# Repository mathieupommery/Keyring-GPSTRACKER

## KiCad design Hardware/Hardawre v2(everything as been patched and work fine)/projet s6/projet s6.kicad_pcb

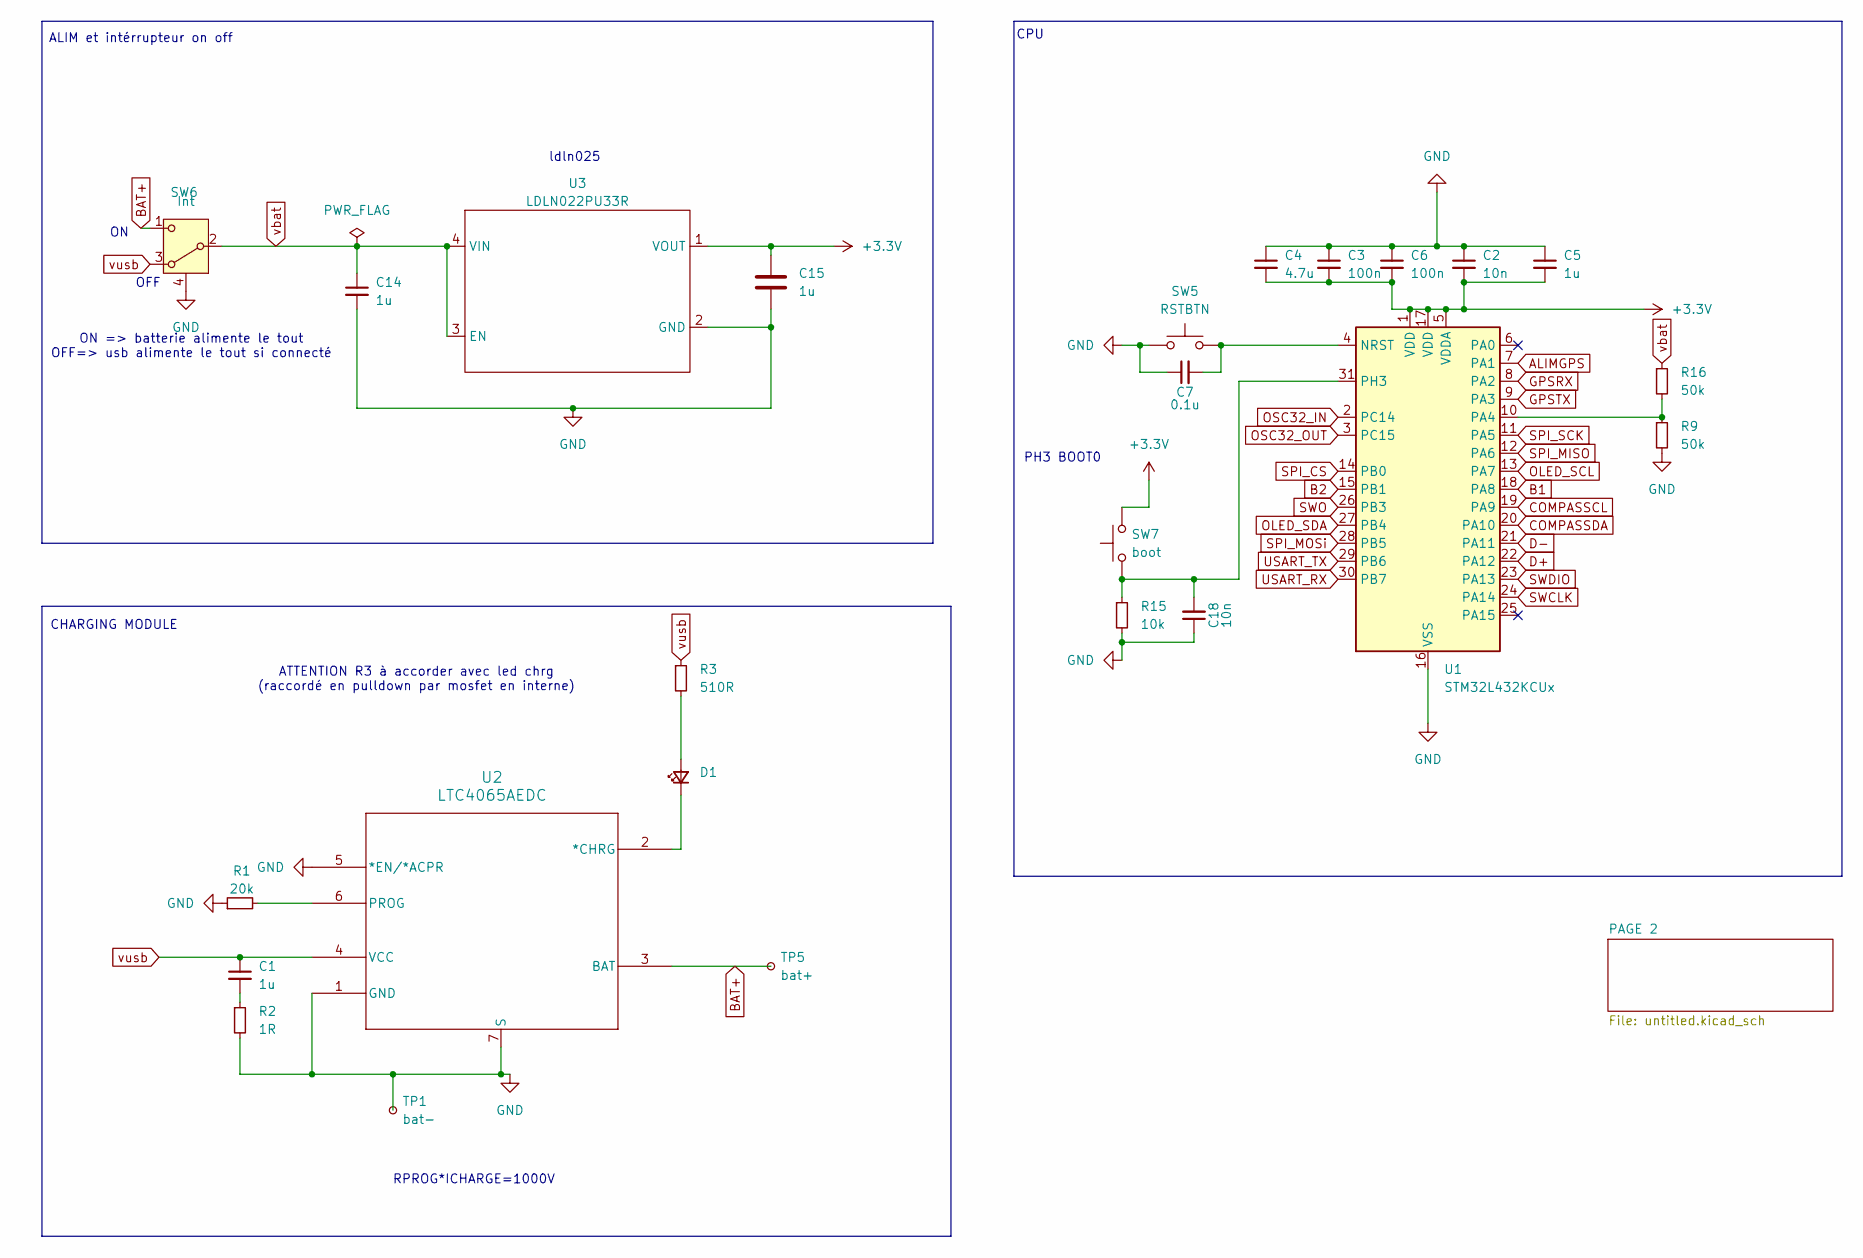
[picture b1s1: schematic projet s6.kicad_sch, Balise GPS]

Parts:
C1, C5, C14, C15: 1u; C_0402_1005Metric_Pad0.74x0.62mm_HandSolder
C2, C18: 10n; C_0402_1005Metric_Pad0.74x0.62mm_HandSolder
C3, C6: 100n; C_0402_1005Metric_Pad0.74x0.62mm_HandSolder
C4: 4.7u; C_0402_1005Metric_Pad0.74x0.62mm_HandSolder
C7: 0.1u; C_0402_1005Metric_Pad0.74x0.62mm_HandSolder
D1: LED_0201_0603Metric_Pad0.64x0.40mm_HandSolder
R1: 20k; R_0402_1005Metric_Pad0.72x0.64mm_HandSolder
R2: 1R; R_0402_1005Metric_Pad0.72x0.64mm_HandSolder
R3: 510R; R_0402_1005Metric_Pad0.72x0.64mm_HandSolder
R9, R16: 50k; R_0402_1005Metric_Pad0.72x0.64mm_HandSolder
R15: 10k; R_0402_1005Metric_Pad0.72x0.64mm_HandSolder
SW5: RSTBTN; SW_KXT3
SW6: Int; SW_PCM
SW7: boot; SW_KXT3
TP1: bat-; TestPoint_THTPad_D1.0mm_Drill0.5mm
TP5: bat+; TestPoint_THTPad_D1.0mm_Drill0.5mm
U1: STM32L432KCUx; QFN-32-1EP_5x5mm_P0.5mm_EP3.45x3.45mm
U2: LTC4065AEDC; DFN-6_DC_LIT
U3: LDLN022PU33R; LDLN025PU33R

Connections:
+3.3V: C2.2, C3.2, C4.2, C5.2, C6.2, C15.1, SW7.2, U1.1 (VDD), U1.5 (VDDA), U1.17 (VDD), U3.1 (VOUT); also elsewhere on the board
ALIMGPS: U1.7 (PA1); also elsewhere on the board
B1: U1.18 (PA8); also elsewhere on the board
B2: U1.15 (PB1); also elsewhere on the board
BAT+: SW6.1 (C), TP5.1, U2.3 (BAT)
COMPASSCL: U1.19 (PA9); also elsewhere on the board
COMPASSDA: U1.20 (PA10); also elsewhere on the board
D+: U1.22 (PA12); also elsewhere on the board
D-: U1.21 (PA11); also elsewhere on the board
GND: C2.1, C3.1, C4.1, C5.1, C6.1, C7.1, C14.2, C15.2, C18.1, R1.1, R2.2, R9.2, R15.2, SW5.1, SW6.4 (S), TP1.1, U1.16 (VSS), U1.32 (VSS), U1.33 (VSS), U2.1 (GND), U2.5 (*EN/*ACPR), U2.7 (S), U3.2 (GND); also elsewhere on the board
GPSRX: U1.8 (PA2); also elsewhere on the board
GPSTX: U1.9 (PA3); also elsewhere on the board
unnamed: C1.2, R2.1
unnamed: D1.2 (A), R3.2
unnamed: D1.1 (K), U2.2 (*CHRG)
unnamed: C7.2, SW5.2, U1.4 (NRST)
unnamed: R9.1, R16.2, U1.10 (PA4)
unnamed: C18.2, R15.1, SW7.1, U1.31 (PH3)
unnamed: R1.2, U2.6 (PROG)
OLED_SCL: U1.13 (PA7); also elsewhere on the board
OLED_SDA: U1.27 (PB4); also elsewhere on the board
OSC32_IN: U1.2 (PC14)
OSC32_OUT: U1.3 (PC15)
SPI_CS: U1.14 (PB0); also elsewhere on the board
SPI_MISO: U1.12 (PA6); also elsewhere on the board
SPI_MOSi: U1.28 (PB5); also elsewhere on the board
SPI_SCK: U1.11 (PA5); also elsewhere on the board
SWCLK: U1.24 (PA14)
SWDIO: U1.23 (PA13)
SWO: U1.26 (PB3)
USART_RX: U1.30 (PB7); also elsewhere on the board
USART_TX: U1.29 (PB6); also elsewhere on the board
vbat: C14.1, R16.1, SW6.2 (B), U3.3 (EN), U3.4 (VIN)
vusb: C1.1, R3.1, SW6.3 (A), U2.4 (VCC); also elsewhere on the board

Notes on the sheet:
PH3 BOOT0
CHARGING MODULE
OFF
ON => batterie alimente le tout OFF=> usb alimente le tout si connecté
ATTENTION R3 à accorder avec led chrg (raccordé en pulldown par mosfet en interne)
ldln025
ALIM et intérrupteur on off
RPROG*ICHARGE=1000V
CPU

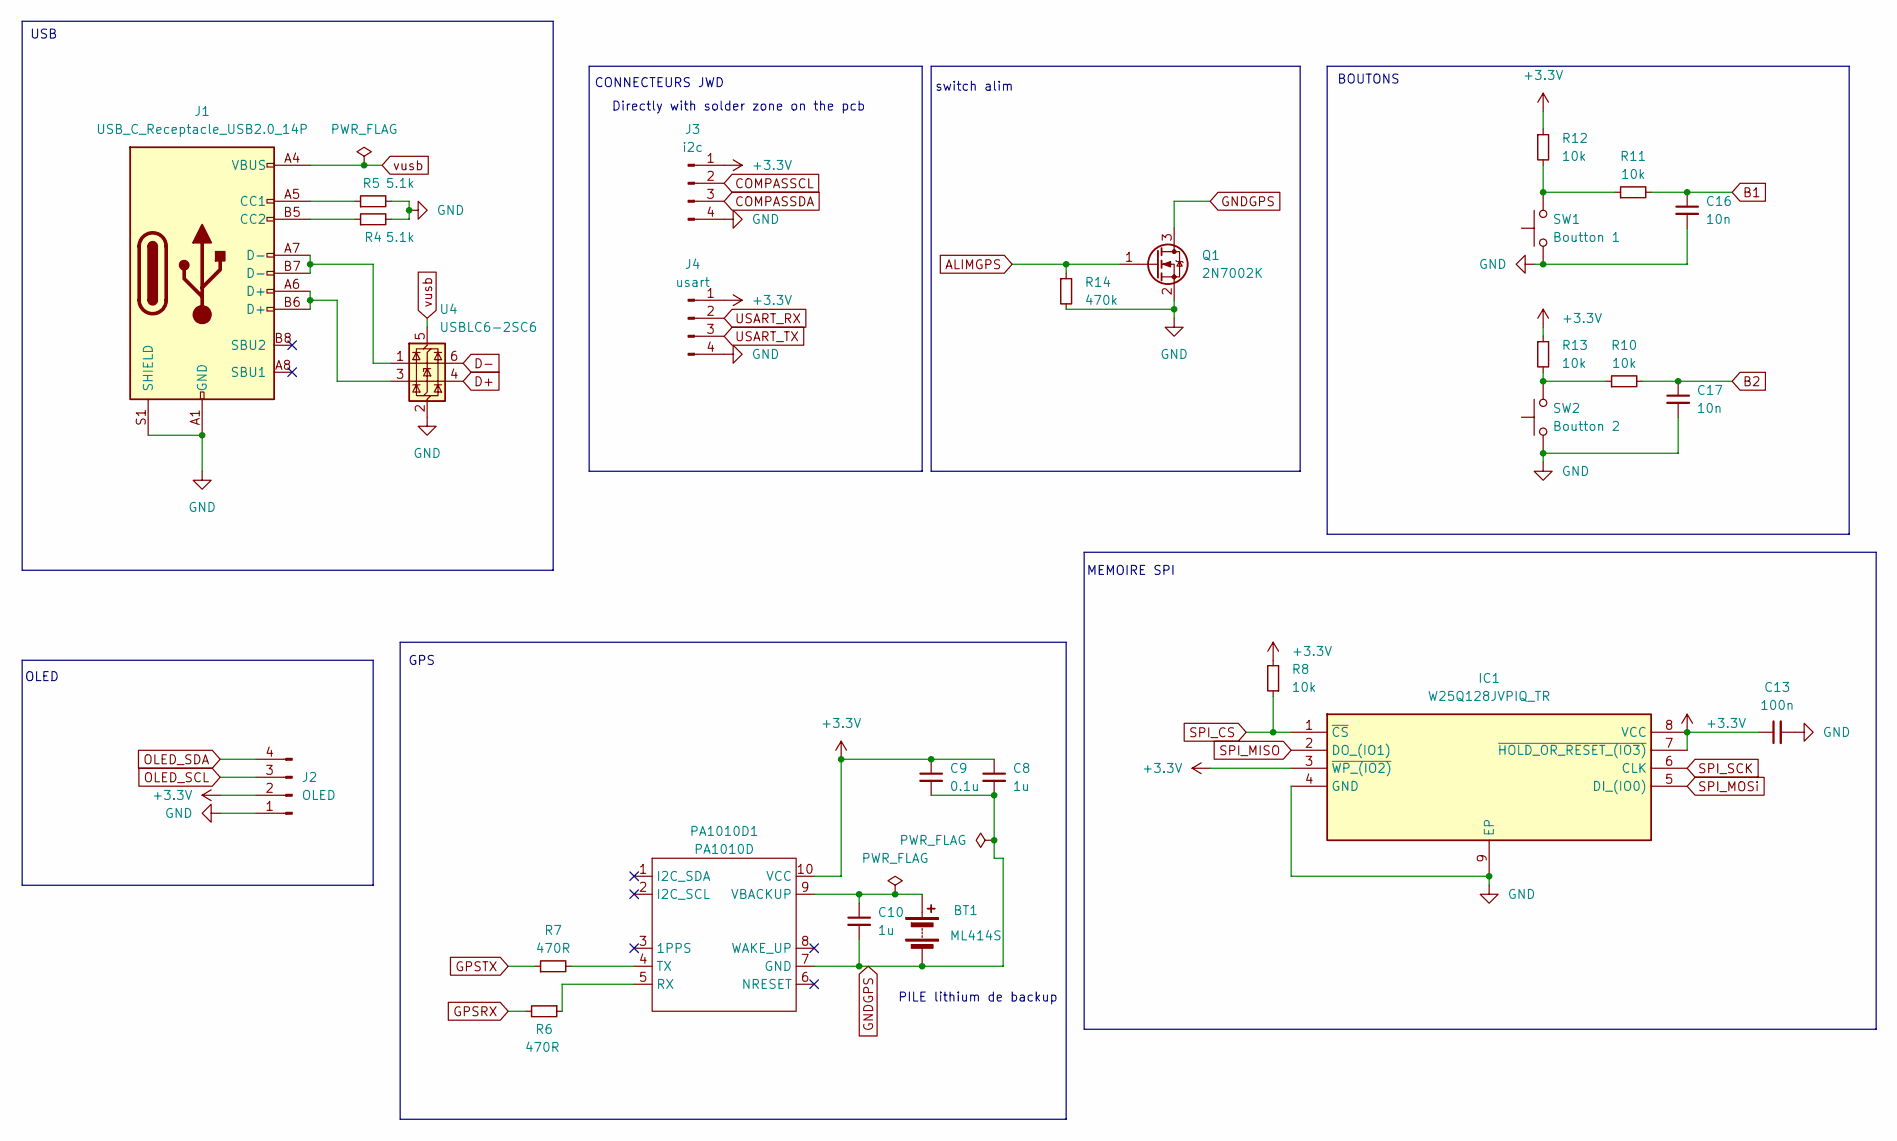
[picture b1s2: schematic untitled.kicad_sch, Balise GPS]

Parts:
BT1: ML414S; MS421R-IV03E
C8, C10: 1u; C_0402_1005Metric_Pad0.74x0.62mm_HandSolder
C9: 0.1u; C_0402_1005Metric_Pad0.74x0.62mm_HandSolder
C13: 100n; C_0402_1005Metric_Pad0.74x0.62mm_HandSolder
C16, C17: 10n; C_0402_1005Metric_Pad0.74x0.62mm_HandSolder
IC1: W25Q128JVPIQ_TR; SON127P600X500X80-9N-D; Manufacturer_Part_Number W25Q128JVPIQ TR; Mouser Part Number 454-W25Q128JVPIQTR
J1: USB_C_Receptacle_USB2.0_14P; USBC-WURTH
J2: OLED; PinSocket_1x04_P2.54mm_Vertical
J3: i2c; JST_SH_BM04B-SRSS-TB_1x04-1MP_P1.00mm_Vertical
J4: usart; JST_SH_BM04B-SRSS-TB_1x04-1MP_P1.00mm_Vertical
PA1010D1: PA1010D
Q1: 2N7002K; 2N7002KQB
R4, R5: 5.1k; R_0402_1005Metric_Pad0.72x0.64mm_HandSolder
R6, R7: 470R; R_0402_1005Metric_Pad0.72x0.64mm_HandSolder
R8, R10, R11, R12, R13: 10k; R_0402_1005Metric_Pad0.72x0.64mm_HandSolder
R14: 470k; R_0402_1005Metric_Pad0.72x0.64mm_HandSolder
SW1: Boutton 1; SW_PTS840
SW2: Boutton 2; SW_PTS840
U4: USBLC6-2SC6; SOT-23-6

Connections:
+3.3V: C8.1, C9.1, C13.1, IC1.3 (~WP_(IO2)), IC1.7 (~HOLD_OR_RESET_(IO3)), IC1.8 (VCC), J2.2, J3.1, J4.1, PA1010D1.10 (VCC), R8.2, R12.1, R13.1; also elsewhere on the board
ALIMGPS: Q1.1 (G), R14.1; also elsewhere on the board
B1: C16.1, R11.2; also elsewhere on the board
B2: C17.1, R10.2; also elsewhere on the board
COMPASSCL: J3.2; also elsewhere on the board
COMPASSDA: J3.3; also elsewhere on the board
D+: U4.4 (I/O2); also elsewhere on the board
D-: U4.6 (I/O1); also elsewhere on the board
GND: C13.2, C16.2, C17.2, IC1.4 (GND), IC1.9 (EP), J1.A1 (GND), J1.A12, J1.B1, J1.B12, J1.S1 (SHIELD), J2.1, J3.4, J3.MP, J4.4, J4.MP, Q1.2 (S), R4.2, R5.2, R14.2, SW1.1, SW2.1, U4.2 (GND); also elsewhere on the board
GNDGPS: BT1.2 (-), C8.2, C9.2, C10.2, PA1010D1.7 (GND), Q1.3 (D)
GPSRX: R6.2; also elsewhere on the board
GPSTX: R7.1; also elsewhere on the board
unnamed: BT1.1 (+), C10.1, PA1010D1.9 (VBACKUP)
unnamed: J1.A5 (CC1), R5.1
unnamed: J1.B5 (CC2), R4.1
unnamed: J1.A6 (D+), J1.B6 (D+), U4.3 (I/O2)
unnamed: J1.A7 (D-), J1.B7 (D-), U4.1 (I/O1)
unnamed: PA1010D1.5 (RX), R6.1
unnamed: PA1010D1.4 (TX), R7.2
unnamed: R10.1, R13.2, SW2.2
unnamed: R11.1, R12.2, SW1.2
OLED_SCL: J2.3; also elsewhere on the board
OLED_SDA: J2.4; also elsewhere on the board
SPI_CS: IC1.1 (~CS), R8.1; also elsewhere on the board
SPI_MISO: IC1.2 (DO_(IO1)); also elsewhere on the board
SPI_MOSi: IC1.5 (DI_(IO0)); also elsewhere on the board
SPI_SCK: IC1.6 (CLK); also elsewhere on the board
USART_RX: J4.2; also elsewhere on the board
USART_TX: J4.3; also elsewhere on the board
vusb: J1.A4 (VBUS), J1.A9, J1.B4, J1.B9, U4.5 (VBUS); also elsewhere on the board

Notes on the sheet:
PILE lithium de backup
OLED
MEMOIRE SPI
switch alim
GPS
Directly with solder zone on the pcb
USB
BOUTONS
CONNECTEURS JWD

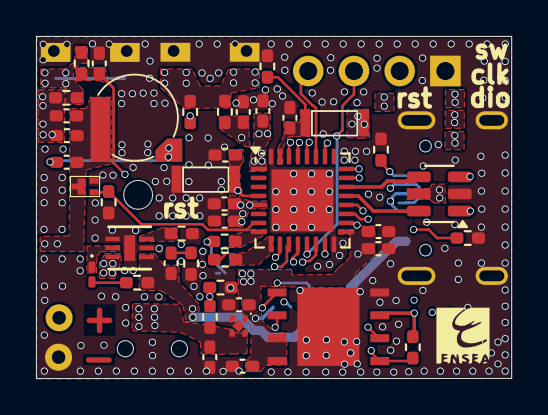
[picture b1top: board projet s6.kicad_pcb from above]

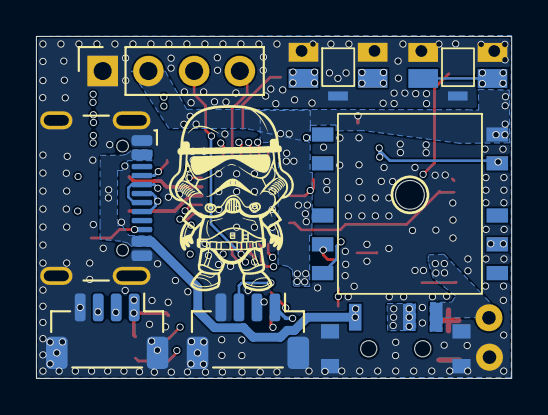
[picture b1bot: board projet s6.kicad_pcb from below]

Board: 4 copper layers, 26.4 x 19.0 mm, 52 parts (8 on the bottom side), 39 nets.

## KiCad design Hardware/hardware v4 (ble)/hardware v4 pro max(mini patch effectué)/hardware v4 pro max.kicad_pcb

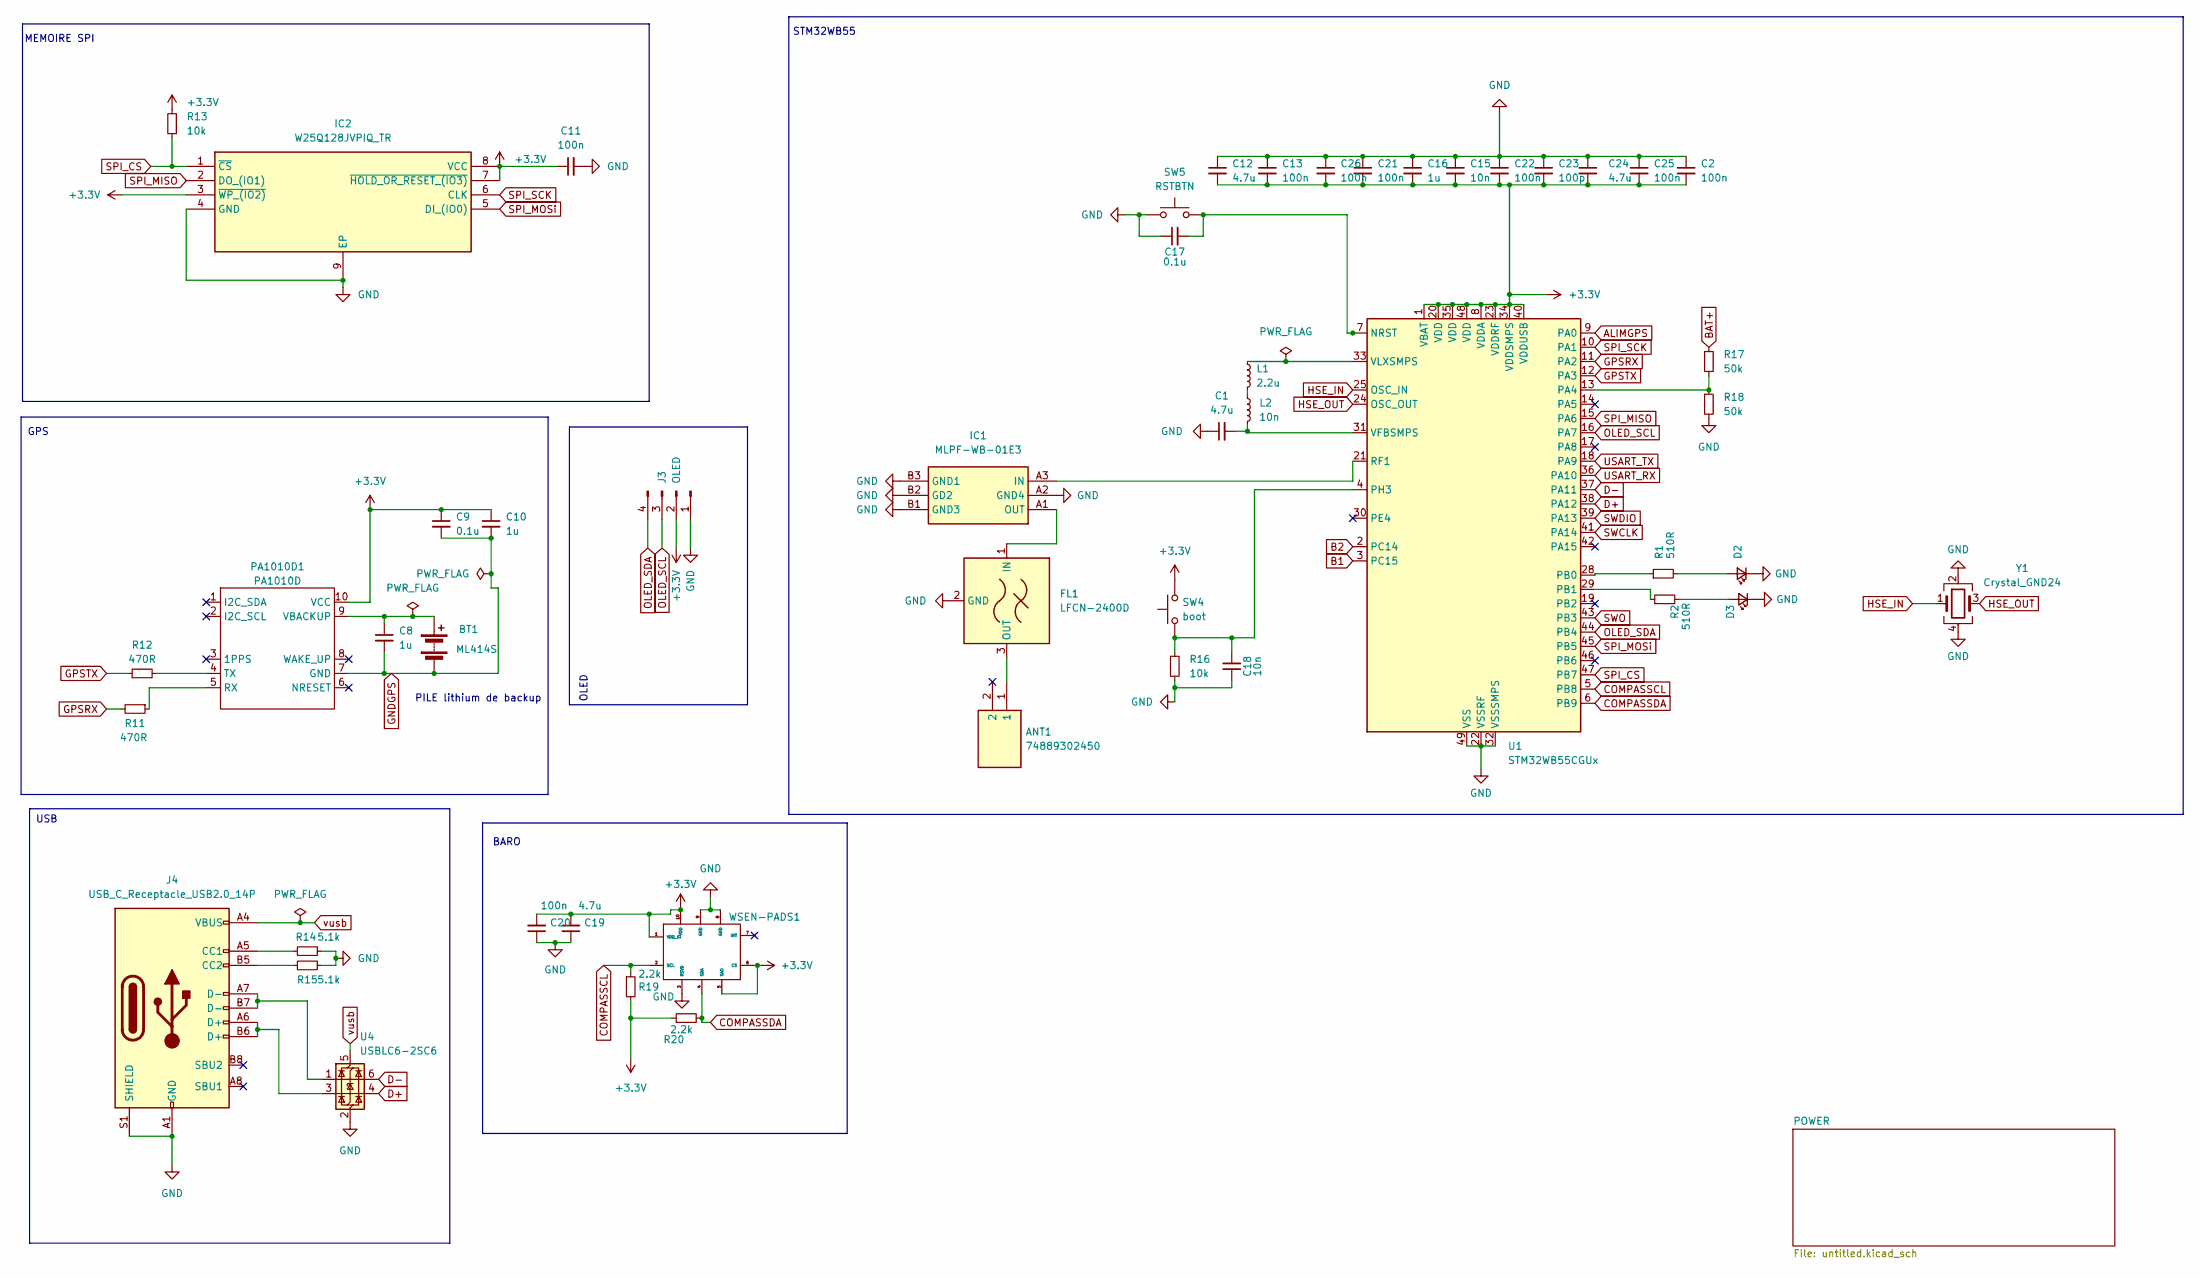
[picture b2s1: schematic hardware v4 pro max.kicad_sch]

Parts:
ANT1: 74889302450; Manufacturer_Part_Number 74889302450; Mouser Part Number 710-74889302450
BT1: ML414S; MS421R-IV03E
C1, C12, C19, C24: 4.7u; C_0402_1005Metric
C2, C11, C13, C20, C21, C22, C25, C26: 100n; C_0402_1005Metric
C8, C10, C16: 1u; C_0402_1005Metric
C9, C17: 0.1u; C_0402_1005Metric
C15, C18: 10n; C_0402_1005Metric
C23: 100p; C_0402_1005Metric
D2, D3: LED_0201_0603Metric_Pad0.64x0.40mm_HandSolder
FL1: LFCN-2400D; DLF162500LT5028A1
IC1: MLPF-WB-01E3; MLPFWB01E3; Manufacturer_Part_Number MLPF-WB-01E3; Mouser Part Number 511-MLPF-WB-01E3
IC2: W25Q128JVPIQ_TR; SON127P600X500X80-9N-D; Manufacturer_Part_Number W25Q128JVPIQ TR; Mouser Part Number 454-W25Q128JVPIQTR
J3: OLED; PinSocket_1x04_P2.54mm_Vertical
J4: USB_C_Receptacle_USB2.0_14P; USBC-WURTH
L1: 2.2u; L_0805_2012Metric
L2: 10n; L_0402_1005Metric
PA1010D1: PA1010D
R1, R2: 510R; R_0402_1005Metric
R11, R12: 470R; R_0402_1005Metric
R13, R16: 10k; R_0402_1005Metric
R14, R15: 5.1k; R_0402_1005Metric
R17, R18: 50k; R_0402_1005Metric
R19, R20: 2.2k; R_0402_1005Metric
SW4: boot; SW_KXT3
SW5: RSTBTN; SW_KXT3
U1: STM32WB55CGUx; QFN-48-1EP_7x7mm_P0.5mm_EP5.6x5.6mm
U4: USBLC6-2SC6; SOT-23-6
WSEN-PADS1: 2511020213301
Y1: Crystal_GND24; 830069494

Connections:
+3.3V: C2.2, C9.1, C10.1, C11.1, C12.2, C13.2, C15.2, C16.2, C19.2, C20.2, C21.2, C22.2, C23.2, C24.2, C25.2, C26.2, IC2.3 (~WP_(IO2)), IC2.7 (~HOLD_OR_RESET_(IO3)), IC2.8 (VCC), J3.2, PA1010D1.10 (VCC), R13.2, R19.2, R20.1, SW4.2, U1.1 (VBAT), U1.8 (VDDA), U1.20 (VDD), U1.23 (VDDRF), U1.34 (VDDSMPS), U1.35 (VDD), U1.40 (VDDUSB), U1.48 (VDD), WSEN-PADS1.1 (VDD_IO), WSEN-PADS1.5 (SAO), WSEN-PADS1.6 (CS), WSEN-PADS1.10 (VDD); also elsewhere on the board
ALIMGPS: U1.9 (PA0); also elsewhere on the board
B1: U1.3 (PC15); also elsewhere on the board
B2: U1.2 (PC14); also elsewhere on the board
BAT+: R17.1; also elsewhere on the board
COMPASSCL: R19.1, U1.5 (PB8), WSEN-PADS1.2 (SCL); also elsewhere on the board
COMPASSDA: R20.2, U1.6 (PB9), WSEN-PADS1.4 (SDA); also elsewhere on the board
D+: U1.38 (PA12), U4.4 (I/O2)
D-: U1.37 (PA11), U4.6 (I/O1)
GND: C1.1, C2.1, C11.2, C12.1, C13.1, C15.1, C16.1, C17.1, C18.1, C19.1, C20.1, C21.1, C22.1, C23.1, C24.1, C25.1, C26.1, D2.1 (K), D3.1 (K), FL1.2 (GND), FL1.4 (GND), IC1.A2 (GND4), IC1.B1 (GND3), IC1.B2 (GD2), IC1.B3 (GND1), IC2.4 (GND), IC2.9 (EP), J3.1, J4.A1 (GND), J4.A12, J4.B1, J4.B12, J4.S1 (SHIELD), R14.2, R15.2, R16.2, R18.2, SW5.1, U1.22 (VSSRF), U1.32 (VSSSMPS), U1.49 (VSS), U4.2 (GND), WSEN-PADS1.3 (RSVD), WSEN-PADS1.8 (GND), WSEN-PADS1.9 (GND), Y1.2, Y1.4; also elsewhere on the board
GNDGPS: BT1.2 (-), C8.2, C9.2, C10.2, PA1010D1.7 (GND); also elsewhere on the board
GPSRX: R11.2, U1.11 (PA2)
GPSTX: R12.1, U1.12 (PA3)
HSE_IN: U1.25 (OSC_IN), Y1.1
HSE_OUT: U1.24 (OSC_OUT), Y1.3
unnamed: BT1.1 (+), C8.1, PA1010D1.9 (VBACKUP)
unnamed: D2.2 (A), R1.2
unnamed: D3.2 (A), R2.2
unnamed: FL1.1 (IN), IC1.A1 (OUT)
unnamed: ANT1.1, FL1.3 (OUT)
unnamed: IC1.A3 (IN), U1.21 (RF1)
unnamed: J4.A5 (CC1), R14.1
unnamed: J4.B5 (CC2), R15.1
unnamed: J4.A6 (D+), J4.B6 (D+), U4.3 (I/O2)
unnamed: J4.A7 (D-), J4.B7 (D-), U4.1 (I/O1)
unnamed: L1.2, L2.1
unnamed: PA1010D1.5 (RX), R11.1
unnamed: PA1010D1.4 (TX), R12.2
unnamed: C17.2, SW5.2, U1.7 (NRST)
unnamed: R17.2, R18.1, U1.13 (PA4)
unnamed: R1.1, U1.28 (PB0)
unnamed: R2.1, U1.29 (PB1)
unnamed: C18.2, R16.1, SW4.1, U1.4 (PH3)
unnamed: C1.2, L2.2, U1.31 (VFBSMPS)
unnamed: L1.1, U1.33 (VLXSMPS)
OLED_SCL: J3.3, U1.16 (PA7)
OLED_SDA: J3.4, U1.44 (PB4)
SPI_CS: IC2.1 (~CS), R13.1, U1.47 (PB7)
SPI_MISO: IC2.2 (DO_(IO1)), U1.15 (PA6)
SPI_MOSi: IC2.5 (DI_(IO0)), U1.45 (PB5)
SPI_SCK: IC2.6 (CLK), U1.10 (PA1)
SWCLK: U1.41 (PA14)
SWDIO: U1.39 (PA13)
SWO: U1.43 (PB3)
USART_RX: U1.36 (PA10); also elsewhere on the board
USART_TX: U1.18 (PA9); also elsewhere on the board
vusb: J4.A4 (VBUS), J4.A9, J4.B4, J4.B9, U4.5 (VBUS); also elsewhere on the board

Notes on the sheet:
MEMOIRE SPI
USB
PILE lithium de backup
BARO
STM32WB55
OLED
GPS

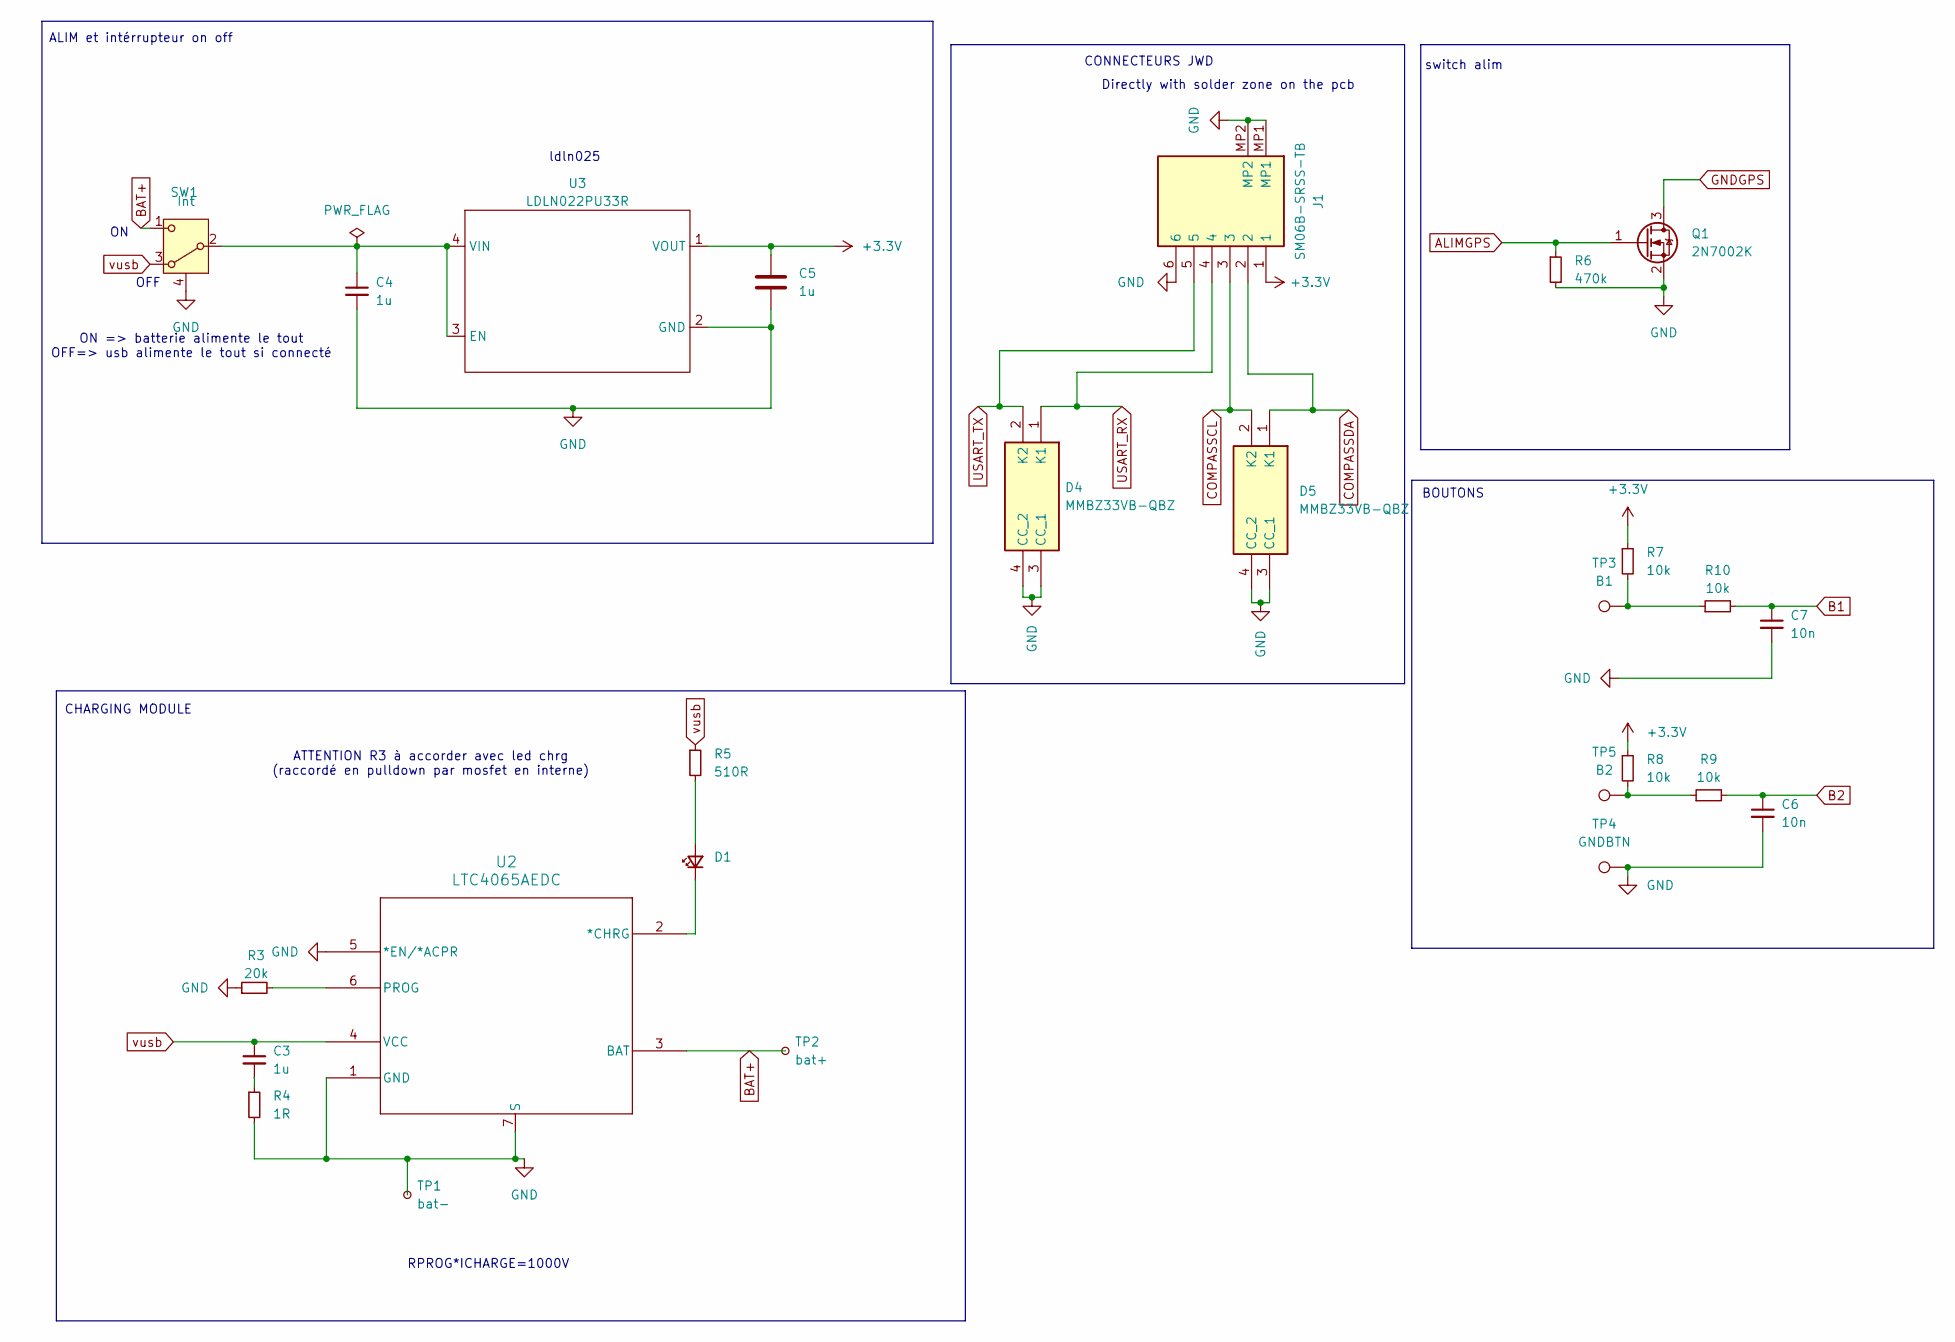
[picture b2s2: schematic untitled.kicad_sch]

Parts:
C3, C4, C5: 1u; C_0402_1005Metric
C6, C7: 10n; C_0402_1005Metric
D1: LED_0201_0603Metric_Pad0.64x0.40mm_HandSolder
D4, D5: MMBZ33VB-QBZ; BC847BQBZ; Manufacturer_Part_Number MMBZ33VB-QBZ; Mouser Part Number 771-MMBZ33VBQBZ
J1: SM06B-SRSS-TB; SM06BSRSSTB; Manufacturer_Part_Number SM06B-SRSS-TB
Q1: 2N7002K; 2N7002KQB
R3: 20k; R_0402_1005Metric
R4: 1R; R_0402_1005Metric
R5: 510R; R_0402_1005Metric
R6: 470k; R_0402_1005Metric
R7, R8, R9, R10: 10k; R_0402_1005Metric
SW1: Int; SW_PCM
TP1: bat-; TestPoint_THTPad_D1.0mm_Drill0.5mm
TP2: bat+; TestPoint_THTPad_D1.0mm_Drill0.5mm
TP3: B1; TestPoint_Pad_1.0x1.0mm
TP4: GNDBTN; TestPoint_Pad_1.0x1.0mm
TP5: B2; TestPoint_Pad_1.0x1.0mm
U2: LTC4065AEDC; DFN-6_DC_LIT
U3: LDLN022PU33R; LDLN025PU33R

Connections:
+3.3V: C5.1, J1.1, R7.1, R8.1, U3.1 (VOUT); also elsewhere on the board
ALIMGPS: Q1.1 (G), R6.1; also elsewhere on the board
B1: C7.1, R10.2; also elsewhere on the board
B2: C6.1, R9.2; also elsewhere on the board
BAT+: SW1.1 (C), TP2.1, U2.3 (BAT); also elsewhere on the board
COMPASSCL: D5.2 (K2), J1.3; also elsewhere on the board
COMPASSDA: D5.1 (K1), J1.2; also elsewhere on the board
GND: C4.2, C5.2, C6.2, C7.2, D4.3 (CC_1), D4.4 (CC_2), D5.3 (CC_1), D5.4 (CC_2), J1.6, J1.MP1, J1.MP2, Q1.2 (S), R3.1, R4.2, R6.2, SW1.4 (S), TP1.1, TP4.1, U2.1 (GND), U2.5 (*EN/*ACPR), U2.7 (S), U3.2 (GND); also elsewhere on the board
GNDGPS: Q1.3 (D); also elsewhere on the board
unnamed: C3.2, R4.1
unnamed: D1.2 (A), R5.2
unnamed: D1.1 (K), U2.2 (*CHRG)
unnamed: R8.2, R9.1, TP5.1
unnamed: R7.2, R10.1, TP3.1
unnamed: C4.1, SW1.2 (B), U3.3 (EN), U3.4 (VIN)
unnamed: R3.2, U2.6 (PROG)
USART_RX: D4.1 (K1), J1.4; also elsewhere on the board
USART_TX: D4.2 (K2), J1.5; also elsewhere on the board
vusb: C3.1, R5.1, SW1.3 (A), U2.4 (VCC); also elsewhere on the board

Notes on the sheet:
ALIM et intérrupteur on off
BOUTONS
ON => batterie alimente le tout OFF=> usb alimente le tout si connecté
switch alim
ldln025
OFF
RPROG*ICHARGE=1000V
Directly with solder zone on the pcb
ATTENTION R3 à accorder avec led chrg (raccordé en pulldown par mosfet en interne)
CONNECTEURS JWD
CHARGING MODULE

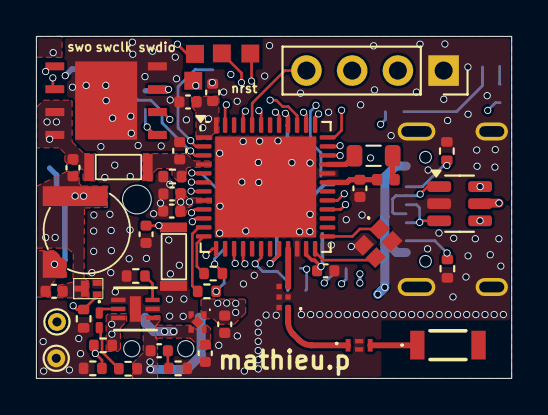
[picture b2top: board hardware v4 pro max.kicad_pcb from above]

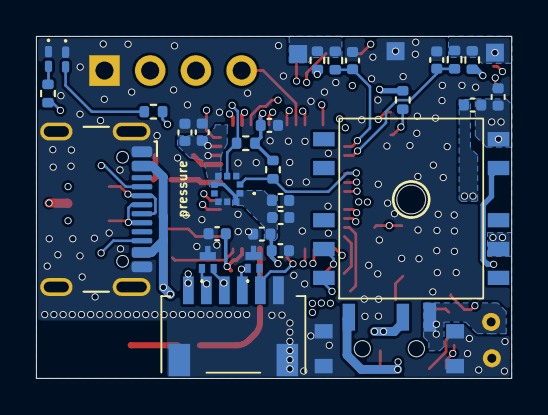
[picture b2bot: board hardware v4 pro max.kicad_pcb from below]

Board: 6 copper layers, 26.4 x 19.0 mm, 76 parts (33 on the bottom side), 51 nets.

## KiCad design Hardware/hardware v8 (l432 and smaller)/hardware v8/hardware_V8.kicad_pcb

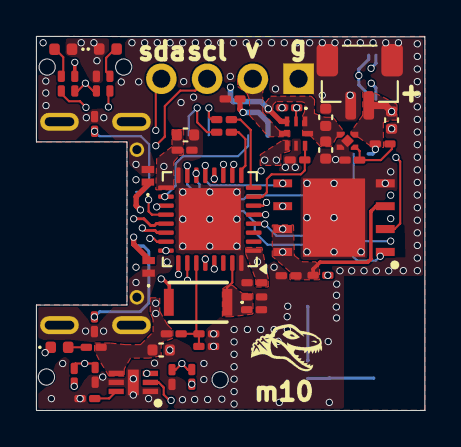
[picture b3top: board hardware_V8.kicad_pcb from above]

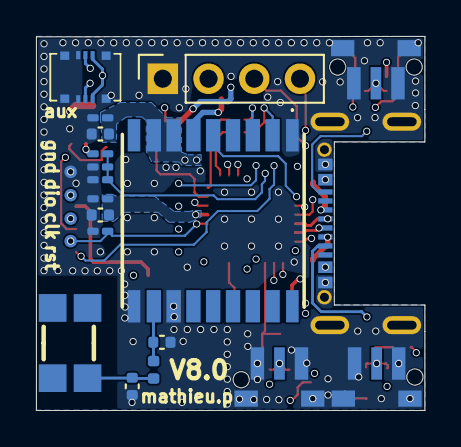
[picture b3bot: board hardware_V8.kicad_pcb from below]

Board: 6 copper layers, 21.6 x 20.8 mm, 68 parts (23 on the bottom side), 43 nets.

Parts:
C1, C4, C5, C16, C29: 1u; C_0402_1005Metric
C2, C3: TBD; C_0402_1005Metric
C6, C7, C8, C10, C11, C13, C14, C18, C20, C25, C26, C27: 100n; C_0201_0603Metric_Pad0.64x0.40mm_HandSolder
C15: 10n; C_0201_0603Metric_Pad0.64x0.40mm_HandSolder
C19, C28: 4.7u; C_0402_1005Metric
D1, D2: PESD5V0S1UL-QYL; PESD5V0S1ULQYL
IC1: TPS22960RSER
IC4: MAX-M10S-00B; MAXM10S00B
IC5: LTC4065EDC#TRMPBF; SON50P200X200X80-7N-D
IC6: W25Q128JVPIQ; SON127P600X500X80-9N-D
J1: USB4720-03-A; USB472003A
J2: 503548-0622; 5035480622
J3: OLED; PinSocket_1x04_P2.54mm_Vertical
L1: TBD; L_0402_1005Metric
LEDBLUE1: 150040BS73240; LED_0402_1005Metric
LEDGREEN1: 150040GS73240; LED_0402_1005Metric
LEDRED1: 150040RS73240; LED_0402_1005Metric
R1, R2, R4, R11, R12: 510R; R_0201_0603Metric_Pad0.64x0.40mm_HandSolder
R3, R10, R16, R19: 470k; R_0201_0603Metric_Pad0.64x0.40mm_HandSolder
R5, R6, R7, R8, R9, R13, R18: 10k; R_0201_0603Metric_Pad0.64x0.40mm_HandSolder
R17: 20k; R_0201_0603Metric_Pad0.64x0.40mm_HandSolder
R20, R21: 100k; R_0201_0603Metric_Pad0.64x0.40mm_HandSolder
R22, R23: 5.1k; R_0201_0603Metric_Pad0.64x0.40mm_HandSolder
S1, S2, S3: PTS845VM20PSMTR4_LFS; PTS845VM20PSMTR4LFS
SW4: boot; KXT341LHS
TP3: SWCLK; pad_0.7mm
TP4: SWDIO; pad_0.7mm
TP5: NRST; pad_0.7mm
TP6: GND; pad_0.7mm
U1: STM32L432KCUx; QFN-32-1EP_5x5mm_P0.5mm_EP3.45x3.45mm
U2: ldln025pu
U3: 146235-0001
U5: JST_SH_BM02B-SRSS-TB_1x02-1MP_P1.00mm_Vertical

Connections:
3.3V_AUX: C11.1, IC1.4 (VOUT1), IC6.3 (~WP_(IO2)), IC6.7 (~HOLD_OR_/RESET_(IO3)), IC6.8 (VCC), J2.1, J2.6, J3.2, R13.2
3.3V_GPS: C26.1, C28.1, IC1.5 (VOUT2), IC4.7 (V_IO), IC4.8 (VCC)
+3.3V: C1.1, C5.1, C10.2, C13.2, C15.2, C16.2, C19.2, IC1.1 (VIN1), IC1.3 (SR), IC1.8 (VIN2), R7.2, R8.2, R9.2, SW4.2, U1.1 (VDD), U1.5 (VDDA), U1.17 (VDD), U2.1 (VOUT)
/ADC_BAT: C8.1, R10.2, R16.2, U1.14 (PB0)
/AUX_EN: IC1.2 (ON1), R21.2, U1.10 (PA4)
/B1: C7.1, R7.1, S1.2 (NO), U1.25 (PA15)
/B2: C6.1, R8.1, S2.2 (NO), U1.26 (PB3)
/B_PW: C20.1, R9.1, S3.2 (NO), U1.6 (PA0)
/D+: D1.1 (K), J1.A6 (DP1), J1.B6 (DP2), U1.22 (PA12)
/D-: D2.2 (A), J1.A7 (DN1), J1.B7 (DN2), U1.21 (PA11)
/GPS_EN: IC1.7 (ON2), R20.2, U1.7 (PA1)
/GPS_EXTINT: IC4.5 (EXTINT), U1.18 (PA8)
/GPS_RX: R12.2, U1.8 (PA2)
/GPS_TX: R11.2, U1.9 (PA3)
/NRST: C27.2, TP5.1, U1.4 (NRST)
/OLED_SCL: J2.5, J3.3, U1.19 (PA9)
/OLED_SDA: J2.2, J3.4, U1.20 (PA10)
/SPI_CLK: IC6.6 (CLK), U1.11 (PA5)
/SPI_CS: IC6.1 (~CS), R13.1, U1.15 (PB1)
/SPI_MISO: IC6.2 (DO_(IO1)), U1.12 (PA6)
/SPI_MOSI: IC6.5 (DI_(IO0)), U1.13 (PA7)
/SWCLK: TP3.1, U1.24 (PA14)
/SWDIO: TP4.1, U1.23 (PA13)
/USB_DETECT: C14.1, R3.1, R19.2, U1.27 (PB4)
BAT+: C4.1, IC5.3 (BAT), R10.1, R18.2, U2.4 (VIN), U5.2
GND: C1.2, C2.2, C3.2, C4.2, C5.2, C6.2, C7.2, C8.2, C10.1, C11.2, C13.1, C14.2, C15.1, C16.1, C18.2, C19.1, C20.2, C25.2, C26.2, C27.1, C28.2, C29.2, D1.2 (A), D2.1 (K), IC1.6 (GND), IC4.1 (GND_1), IC4.10 (GND_2), IC4.12 (GND_3), IC5.1 (GND), IC5.5 (~EN), IC5.7 (EP), IC6.4 (GND_1), IC6.9 (GND_2), J1.A1 (GND_1), J1.A12 (GND_2), J1.MH1, J1.MH2, J1.MH3, J1.MH4, J1.MH5, J1.MH6, J2.3, J2.4, J2.7, J2.8, J2.9, J2.10, J3.1, LEDBLUE1.1 (K), LEDGREEN1.1 (K), R5.1, R6.2, R16.1, R17.2, R19.1, R20.1, R21.1, R22.2, R23.2, S1.1 (COM_1), S1.3 (COM_2), S1.MP1, S1.MP2, S2.1 (COM_1), S2.3 (COM_2), S2.MP1, S2.MP2, S3.1 (COM_1), S3.3 (COM_2), S3.MP1, S3.MP2, TP6.1, U1.16 (VSS), U1.32 (VSS), U1.33 (VSS), U2.2 (GND), U5.1, U5.MP
unnamed: C3.1, L1.1, U3.1
unnamed: C2.1, IC4.11 (RF_IN), L1.2
unnamed: IC4.3 (RXD), R12.1
unnamed: IC4.2 (TXD), R11.1
unnamed: C25.1, IC4.6 (V_BCKP)
unnamed: IC5.6 (PROG), R17.1
unnamed: IC5.2 (~CHRG), LEDRED1.1 (K)
unnamed: J1.A5 (CC1), R22.1
unnamed: J1.B5 (CC2), R23.1
unnamed: LEDBLUE1.2 (A), R2.2
unnamed: LEDGREEN1.2 (A), R1.2
unnamed: LEDRED1.2 (A), R4.1
unnamed: R1.1, U1.28 (PB5)
unnamed: R2.1, U1.29 (PB6)
unnamed: C18.1, R6.1, SW4.1, U1.31 (PH3)
unnamed: R5.2, R18.1, U2.3 (EN)
vusb: C29.1, IC5.4 (VCC), J1.A4 (VBUS_1), J1.A9 (VBUS_2), R3.2, R4.2
